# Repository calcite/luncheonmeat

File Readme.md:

# luncheonmeat

## Hardware

Device PCB was designed using KiCAD 5.1. For more info visit KiCAD website [kicad.org](https://kicad.org/download/) 

## Firmware

### Dependencies

```shell
sudo apt-get install gcc-avr binutils-avr avr-libc gdb-avr avrdude
```

> Note: ``ATMega328PB`` is new revision from 2017. avr-libc may not have support for this device. To add support please see how its done in .devcontainer/Dockerfile.

### Build

```shell
cd firmware
make
```

### Flashing

Flashing the device using AVR Dragon ISP:

```shell
make program
```

Set fuses **this is done only once**:

```shell
make program-fuses
```

> Note: ``make`` will internally run ``avrdude`` with correct atributes. 

Bare avrdude flashing command:

```shell
avrdude -p atmega328pb -P usb -c dragon_isp    -U flash:w:luncheonmeat.hex -U eeprom:w:luncheonmeat.eep
```

### Serial Bootloader

Generating ``defines.h`` file:
```shell
cd firmware/bootloader
./preprocessor.sh atmega328pb 2048 PORTB PINB0 8000000 19200
make
make program
make program-fuses
```

Reading target fuses:
```shell
avrdude -p atmega328pb -P usb -c dragon_isp -U efuse:r:-:h
```

To enter bootloader hold ''5'' button and reset the device.

## Resources

- [fuses calculator](http://eleccelerator.com/fusecalc/fusecalc.php?chip=atmega328p&LOW=E2&HIGH=D8&EXTENDED=F7&LOCKBIT=FF)

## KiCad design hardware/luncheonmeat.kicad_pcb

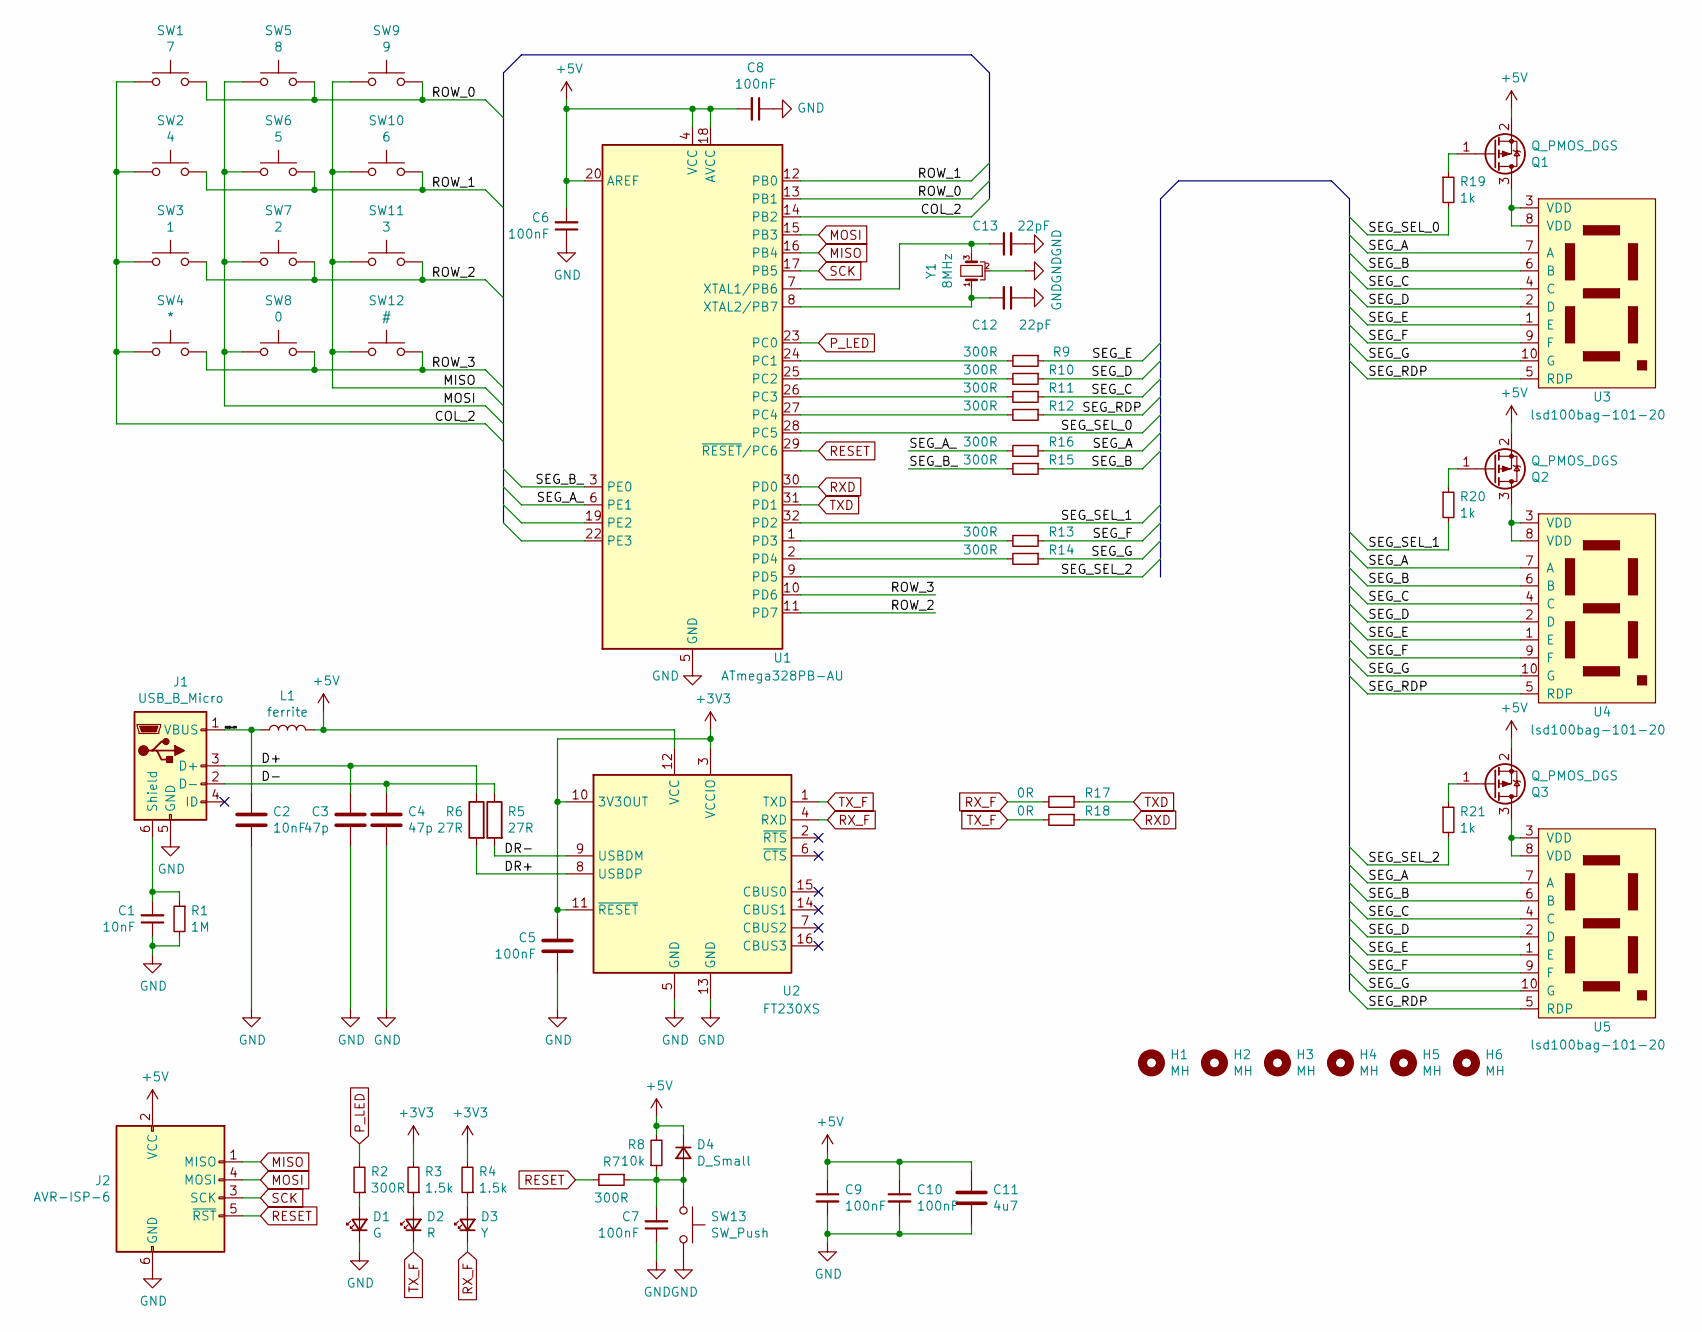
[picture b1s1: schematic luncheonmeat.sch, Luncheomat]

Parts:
C1, C2: 10nF; C_0805_2012Metric_Pad1.18x1.45mm_HandSolder
C3, C4: 47p; C_0805_2012Metric_Pad1.18x1.45mm_HandSolder
C5, C6, C7, C8, C9, C10: 100nF; C_0805_2012Metric_Pad1.18x1.45mm_HandSolder
C11: 4u7; C_0603_1608Metric_Pad1.05x0.95mm_HandSolder
C12, C13: 22pF; C_0603_1608Metric_Pad1.08x0.95mm_HandSolder
D1: G; LED_0805_2012Metric_Castellated
D2: R; LED_0805_2012Metric_Castellated
D3: Y; LED_0805_2012Metric_Castellated
D4: D_Small; D_0805_2012Metric
H1, H2, H3, H4, H5, H6: MH; MountingHole_3.2mm_M3_DIN965
J1: USB_B_Micro; USB_Micro-B_Wuerth_629105150521_CircularHoles
J2: AVR-ISP-6; IDC-Header_2x03_P2.54mm_Vertical
L1: ferrite; L_0805_2012Metric_Pad1.15x1.40mm_HandSolder
Q1, Q2, Q3: Q_PMOS_DGS; SOT-23
R1: 1M; R_0805_2012Metric_Pad1.20x1.40mm_HandSolder
R2, R7, R9, R10, R11, R12, R13, R14, R15, R16: 300R; R_0805_2012Metric_Pad1.20x1.40mm_HandSolder
R3, R4: 1.5k; R_0805_2012Metric_Pad1.20x1.40mm_HandSolder
R5, R6: 27R; R_0805_2012Metric_Pad1.20x1.40mm_HandSolder
R8: 10k; R_0805_2012Metric_Pad1.20x1.40mm_HandSolder
R17, R18: 0R; R_0805_2012Metric_Pad1.20x1.40mm_HandSolder
R19, R20, R21: 1k; R_0805_2012Metric_Pad1.20x1.40mm_HandSolder
SW1: 7; SW_PUSH_6mm
SW2: 4; SW_PUSH_6mm
SW3: 1; SW_PUSH_6mm
SW4: *; SW_PUSH_6mm
SW5: 8; SW_PUSH_6mm
SW6: 5; SW_PUSH_6mm
SW7: 2; SW_PUSH_6mm
SW8: 0; SW_PUSH_6mm
SW9: 9; SW_PUSH_6mm
SW10: 6; SW_PUSH_6mm
SW11: 3; SW_PUSH_6mm
SW12: #; SW_PUSH_6mm
SW13: SW_Push; SW_Push_1P1T_NO_CK_KSC7xxJ
U1: ATmega328PB-AU; TQFP-32_7x7mm_P0.8mm
U2: FT230XS; SSOP-16_3.9x4.9mm_P0.635mm
U3, U4, U5: lsd100bag-101-20; lsd100bag-101
Y1: 8MHz; Crystal_SMD_0603-4Pin_6.0x3.5mm_HandSoldering

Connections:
+3V3: C5.2, R3.2, R4.2, U2.3 (VCCIO), U2.10 (3V3OUT), U2.11 (~RESET)
+5V: C6.2, C8.2, C9.1, C10.1, C11.1, D4.1 (K), J2.2 (VCC), L1.2, Q1.2 (S), Q2.2 (S), Q3.2 (S), R8.2, U1.4 (VCC), U1.18 (AVCC), U1.20 (AREF), U2.12 (VCC)
/COL_2: SW1.2, SW2.2, SW3.2, SW4.2, U1.14 (PB2)
/D+: C3.2, J1.3 (D+), R6.1
/D-: C4.1, J1.2 (D-), R5.1
/DR+: R6.2, U2.8 (USBDP)
/DR-: R5.2, U2.9 (USBDM)
/ROW_0: SW1.1, SW5.1, SW9.1, U1.13 (PB1)
/ROW_1: SW2.1, SW6.1, SW10.1, U1.12 (PB0)
/ROW_2: SW3.1, SW7.1, SW11.1, U1.11 (PD7)
/ROW_3: SW4.1, SW8.1, SW12.1, U1.10 (PD6)
/SEG_A: R16.1, U3.7 (A), U4.7 (A), U5.7 (A)
/SEG_A_: R16.2, U1.6 (PE1)
/SEG_B: R15.1, U3.6 (B), U4.6 (B), U5.6 (B)
/SEG_B_: R15.2, U1.3 (PE0)
/SEG_C: R11.1, U3.4 (C), U4.4 (C), U5.4 (C)
/SEG_D: R10.1, U3.2 (D), U4.2 (D), U5.2 (D)
/SEG_E: R9.1, U3.1 (E), U4.1 (E), U5.1 (E)
/SEG_F: R13.1, U3.9 (F), U4.9 (F), U5.9 (F)
/SEG_G: R14.1, U3.10 (G), U4.10 (G), U5.10 (G)
/SEG_RDP: R12.1, U3.5 (RDP), U4.5 (RDP), U5.5 (RDP)
/SEG_SEL_0: R19.2, U1.28 (PC5)
/SEG_SEL_1: R20.2, U1.32 (PD2)
/SEG_SEL_2: R21.2, U1.9 (PD5)
/USB+5V: C2.2, J1.1 (VBUS), L1.1
GND: C1.1, C2.1, C3.1, C4.2, C5.1, C6.1, C7.1, C8.1, C9.2, C10.2, C11.2, C12.1, C13.2, D1.1 (K), J1.5 (GND), J2.6 (GND), R1.2, SW13.2, U1.5 (GND), U1.21 (GND), U2.5 (GND), U2.13 (GND), Y1.2
MISO: J2.1 (MISO), SW9.2, SW10.2, SW11.2, SW12.2, U1.16 (PB4)
MOSI: J2.4 (MOSI), SW5.2, SW6.2, SW7.2, SW8.2, U1.15 (PB3)
unnamed: C1.2, J1.6 (Shield), R1.1
unnamed: C7.2, D4.2 (A), R7.1, R8.1, SW13.1
unnamed: C12.2, U1.8 (XTAL2/PB7), Y1.1
unnamed: C13.1, U1.7 (XTAL1/PB6), Y1.3
unnamed: D1.2 (A), R2.1
unnamed: D2.2 (A), R3.1
unnamed: D3.2 (A), R4.1
unnamed: Q1.1 (G), R19.1
unnamed: Q1.3 (D), U3.3 (VDD), U3.8 (VDD)
unnamed: Q2.1 (G), R20.1
unnamed: Q2.3 (D), U4.3 (VDD), U4.8 (VDD)
unnamed: Q3.1 (G), R21.1
unnamed: Q3.3 (D), U5.3 (VDD), U5.8 (VDD)
unnamed: R9.2, U1.24 (PC1)
unnamed: R10.2, U1.25 (PC2)
unnamed: R11.2, U1.26 (PC3)
unnamed: R12.2, U1.27 (PC4)
unnamed: R13.2, U1.1 (PD3)
unnamed: R14.2, U1.2 (PD4)
P_LED: R2.2, U1.23 (PC0)
RESET: J2.5 (~RST), R7.2, U1.29 (~RESET~/PC6)
RXD: R18.1, U1.30 (PD0)
RX_F: D3.1 (K), R17.2, U2.4 (RXD)
SCK: J2.3 (SCK), U1.17 (PB5)
TXD: R17.1, U1.31 (PD1)
TX_F: D2.1 (K), R18.2, U2.1 (TXD)

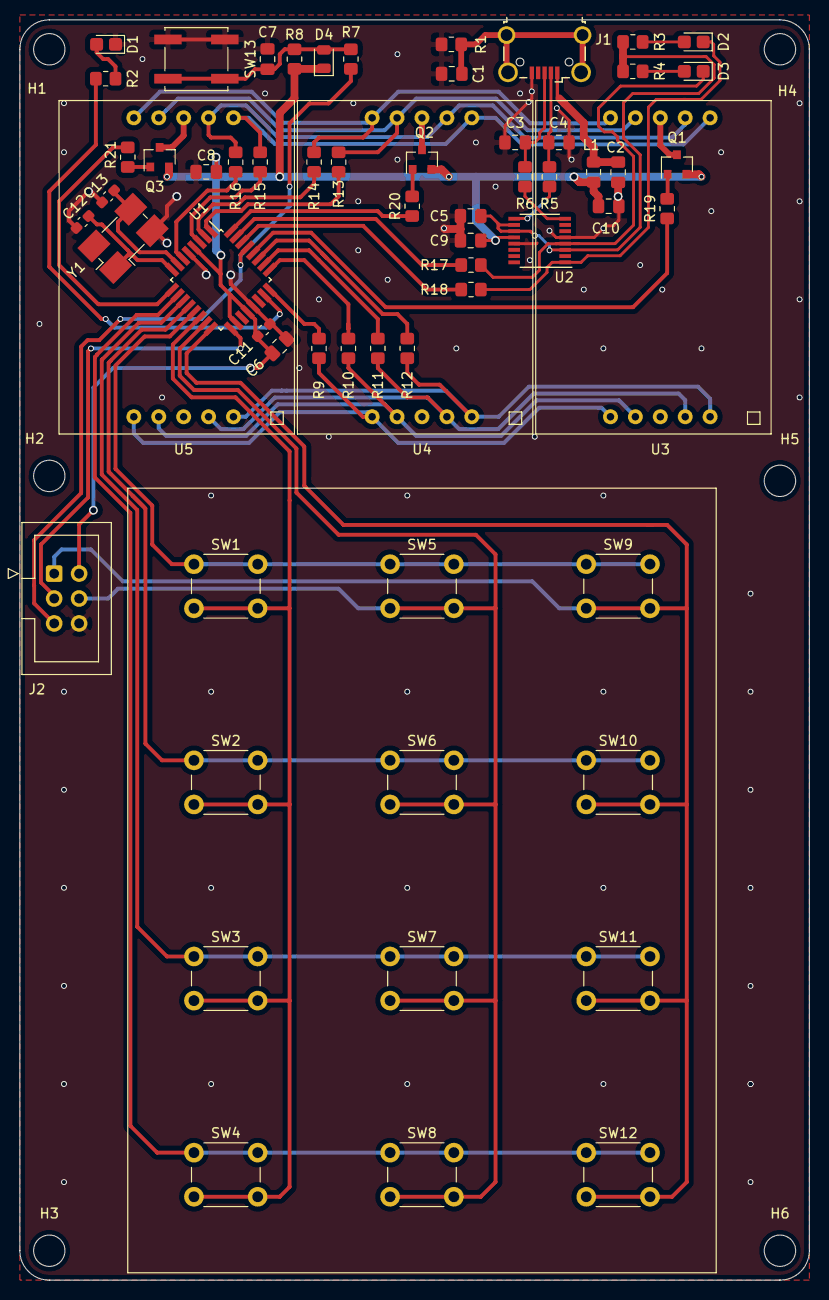
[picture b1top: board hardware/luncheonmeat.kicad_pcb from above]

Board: 2 copper layers, 80.5 x 128.5 mm, 69 parts (0 on the bottom side), 54 nets.

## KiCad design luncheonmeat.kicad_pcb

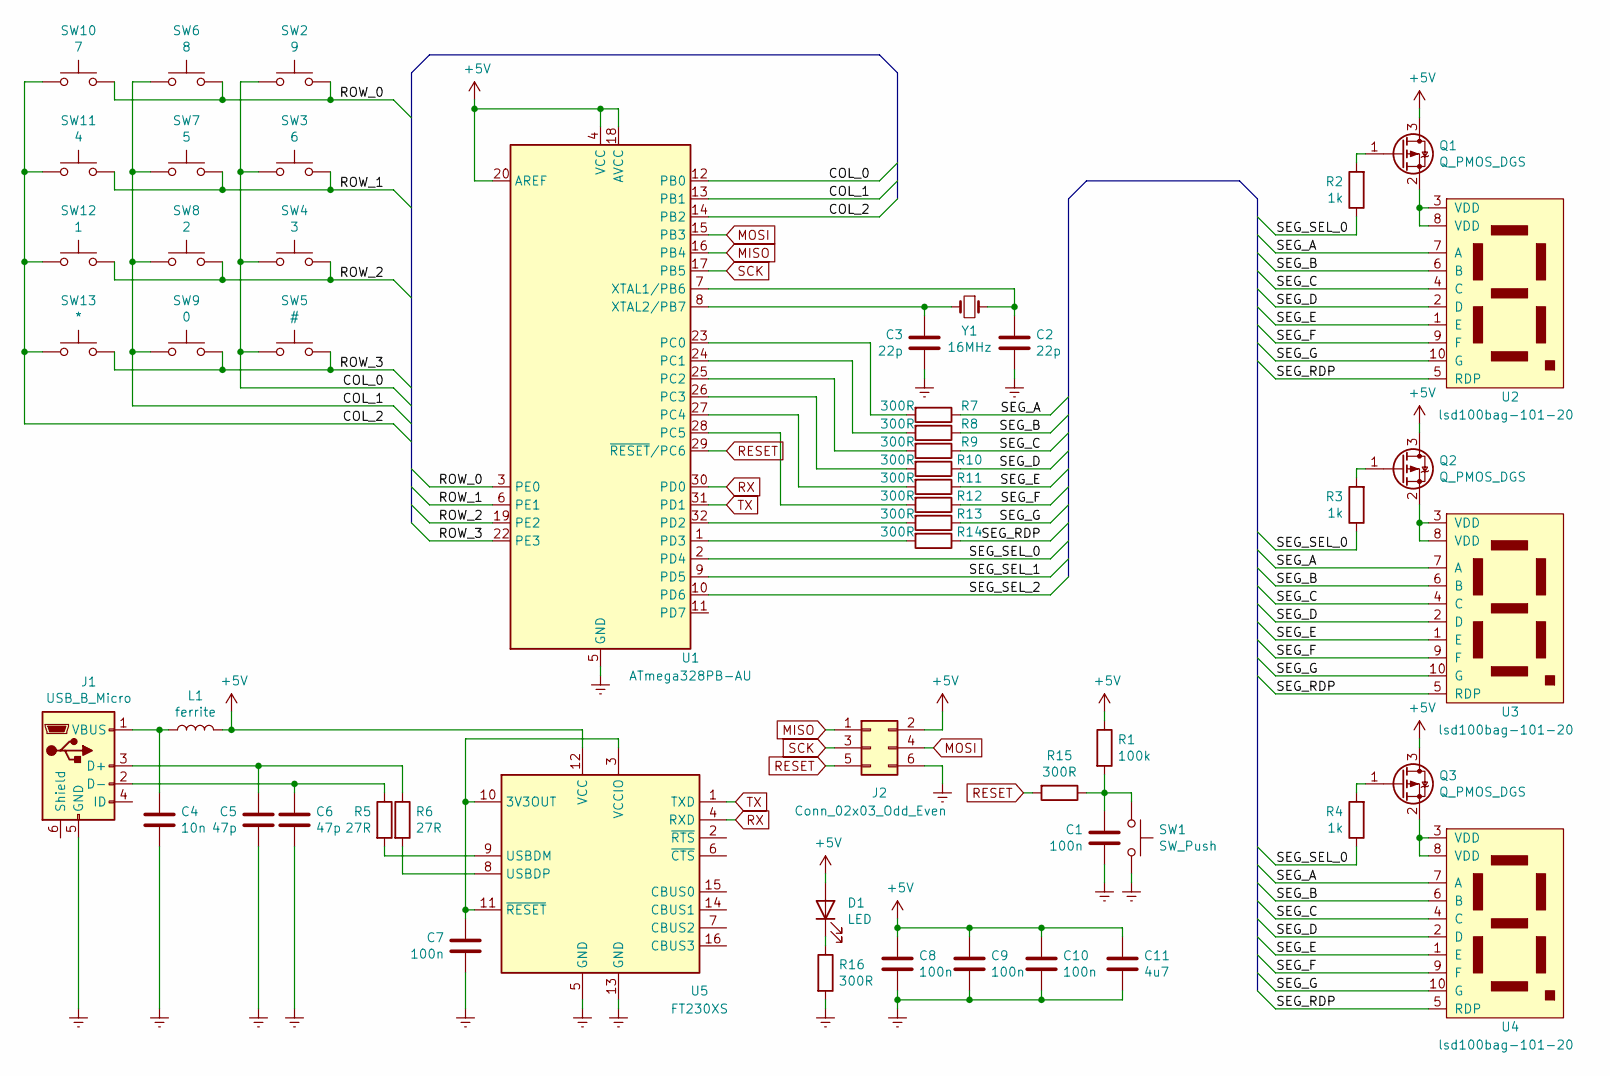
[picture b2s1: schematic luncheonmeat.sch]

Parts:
C1, C7, C8, C9, C10: 100n; C_0603_1608Metric_Pad1.05x0.95mm_HandSolder
C2, C3: 22p; C_0603_1608Metric_Pad1.05x0.95mm_HandSolder
C4: 10n; C_0603_1608Metric_Pad1.05x0.95mm_HandSolder
C5, C6: 47p; C_0603_1608Metric_Pad1.05x0.95mm_HandSolder
C11: 4u7; C_0603_1608Metric_Pad1.05x0.95mm_HandSolder
D1: LED; D_0603_1608Metric_Pad1.05x0.95mm_HandSolder
J1: USB_B_Micro; USB_Micro-B_Wuerth_629105150521_CircularHoles
J2: Conn_02x03_Odd_Even; PinHeader_2x03_P2.54mm_Vertical
L1: ferrite; L_0805_2012Metric_Pad1.15x1.40mm_HandSolder
Q1, Q2, Q3: Q_PMOS_DGS; SOT-23
R1: 100k; R_0603_1608Metric_Pad1.05x0.95mm_HandSolder
R2, R3, R4: 1k; R_0603_1608Metric_Pad1.05x0.95mm_HandSolder
R5, R6: 27R; R_0603_1608Metric_Pad1.05x0.95mm_HandSolder
R7, R8, R9, R10, R11, R12, R13, R14, R15, R16: 300R; R_0603_1608Metric_Pad1.05x0.95mm_HandSolder
SW1: SW_Push; PinHeader_1x02_P2.54mm_Vertical
SW2: 9; SW_PUSH_6mm
SW3: 6; SW_PUSH_6mm
SW4: 3; SW_PUSH_6mm
SW5: #; SW_PUSH_6mm
SW6: 8; SW_PUSH_6mm
SW7: 5; SW_PUSH_6mm
SW8: 2; SW_PUSH_6mm
SW9: 0; SW_PUSH_6mm
SW10: 7; SW_PUSH_6mm
SW11: 4; SW_PUSH_6mm
SW12: 1; SW_PUSH_6mm
SW13: *; SW_PUSH_6mm
U1: ATmega328PB-AU; TQFP-32_7x7mm_P0.8mm
U2, U3, U4: lsd100bag-101-20
U5: FT230XS; SSOP-16_3.9x4.9mm_P0.635mm
Y1: 16MHz; Crystal_HC49-4H_Vertical

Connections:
+5V: C8.1, C9.1, C10.1, C11.1, D1.2 (A), J2.2, L1.2, Q1.3 (D), Q2.3 (D), Q3.3 (D), R1.1, U1.4 (VCC), U1.18 (AVCC), U1.20 (AREF), U5.12 (VCC)
/COL_0: SW2.2, SW3.2, SW4.2, SW5.2, U1.12 (PB0)
/COL_1: SW6.2, SW7.2, SW8.2, SW9.2, U1.13 (PB1)
/COL_2: SW10.2, SW11.2, SW12.2, SW13.2, U1.14 (PB2)
/D+: C5.2, J1.3 (D+), R6.1
/D-: C6.1, J1.2 (D-), R5.1
/DR+: R6.2, U5.8 (USBDP)
/DR-: R5.2, U5.9 (USBDM)
/ROW_0: SW2.1, SW6.1, SW10.1, U1.3 (PE0)
/ROW_1: SW3.1, SW7.1, SW11.1, U1.6 (PE1)
/ROW_2: SW4.1, SW8.1, SW12.1, U1.19 (PE2)
/ROW_3: SW5.1, SW9.1, SW13.1, U1.22 (PE3)
/SEG_A: R7.1, U2.7 (A), U3.7 (A), U4.7 (A)
/SEG_B: R8.1, U2.6 (B), U3.6 (B), U4.6 (B)
/SEG_C: R9.1, U2.4 (C), U3.4 (C), U4.4 (C)
/SEG_D: R10.1, U2.2 (D), U3.2 (D), U4.2 (D)
/SEG_E: R11.1, U2.1 (E), U3.1 (E), U4.1 (E)
/SEG_F: R12.1, U2.9 (F), U3.9 (F), U4.9 (F)
/SEG_G: R13.1, U2.10 (G), U3.10 (G), U4.10 (G)
/SEG_RDP: R14.1, U2.5 (RDP), U3.5 (RDP), U4.5 (RDP)
Earth: C1.1, C2.1, C3.2, C4.1, C5.1, C6.2, C7.1, C8.2, C9.2, C10.2, C11.2, J1.5 (GND), J2.6, R16.2, SW1.2, U1.5 (GND), U1.21 (GND), U5.5 (GND), U5.13 (GND)
MISO: J2.1, U1.16 (PB4)
MOSI: J2.4, U1.15 (PB3)
unnamed: C1.2, R1.2, R15.1, SW1.1
unnamed: C2.2, U1.7 (XTAL1/PB6), Y1.1
unnamed: C3.1, U1.8 (XTAL2/PB7), Y1.2
unnamed: C4.2, J1.1 (VBUS), L1.1
unnamed: C7.2, U5.3 (VCCIO), U5.10 (3V3OUT), U5.11 (~RESET)
unnamed: D1.1 (K), R16.1
unnamed: Q1.1 (G), R2.2
unnamed: Q1.2 (S), U2.3 (VDD), U2.8 (VDD)
unnamed: Q2.1 (G), R3.2
unnamed: Q2.2 (S), U3.3 (VDD), U3.8 (VDD)
unnamed: Q3.1 (G), R4.2
unnamed: Q3.2 (S), U4.3 (VDD), U4.8 (VDD)
unnamed: R7.2, U1.23 (PC0)
unnamed: R8.2, U1.24 (PC1)
unnamed: R9.2, U1.25 (PC2)
unnamed: R10.2, U1.26 (PC3)
unnamed: R11.2, U1.27 (PC4)
unnamed: R12.2, U1.28 (PC5)
unnamed: R13.2, U1.32 (PD2)
unnamed: R14.2, U1.1 (PD3)
RESET: J2.5, R15.2, U1.29 (~RESET~/PC6)
RX: U1.30 (PD0), U5.4 (RXD)
SCK: J2.3, U1.17 (PB5)
TX: U1.31 (PD1), U5.1 (TXD)

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
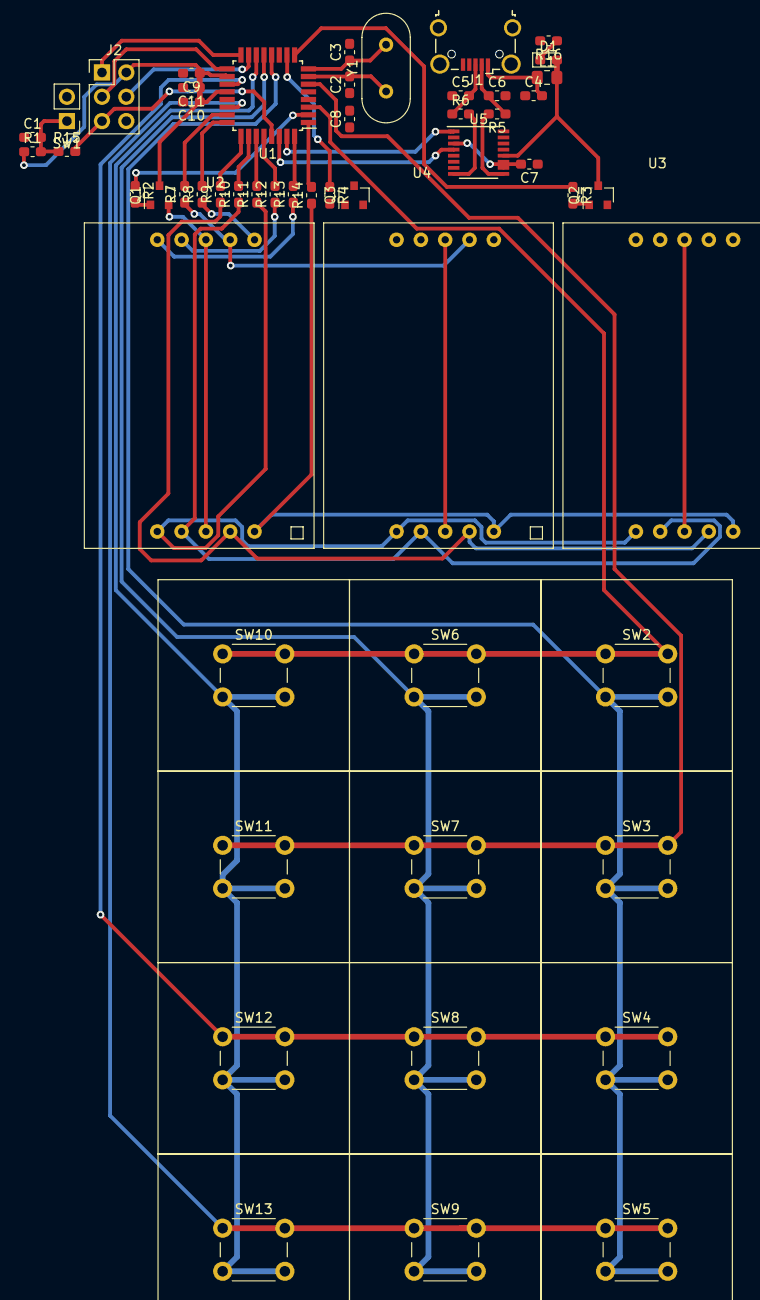
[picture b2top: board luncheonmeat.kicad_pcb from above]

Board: 2 copper layers, 53 parts (0 on the bottom side), 50 nets.

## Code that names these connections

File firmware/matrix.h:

/*
 *  Copyright (C) 2017 Juraj Giertl
 *  All Rights Reserved.
 */
#ifndef _MATRIX_H_
#define _MATRIX_H_

#include <avr/io.h>
#include <stdbool.h>
#include "hw_def.h"

#define ROW_0_PIN		PINB1
#define ROW_1_PIN		PINB0
#define ROW_2_PIN		PIND7
#define ROW_3_PIN		PIND6
#define COL_0_PIN		PINB4
#define COL_1_PIN		PINB3
#define COL_2_PIN		PINB2

#define ROW_0_DDR		DDRB
#define ROW_1_DDR		DDRB
#define ROW_2_DDR		DDRD
#define ROW_3_DDR		DDRD
#define COL_0_DDR		DDRB
#define COL_1_DDR		DDRB
#define COL_2_DDR		DDRB

#define ROW_0_PORT      PORTB
#define ROW_1_PORT      PORTB
#define ROW_2_PORT      PORTD
#define ROW_3_PORT      PORTD
#define COL_0_PORT      PORTB
#define COL_1_PORT      PORTB
#define COL_2_PORT      PORTB

#define IDLE_CNT_MAX 610; // is 20 seconds, s * 30.5 
#define MK_KEY_CLEAR (0x2A)
#define MK_KEY_ENTER (0x23)


#define MK_UNIT_DELAY_MS                    (1)
#define MK_LONG_PUSH_TRESHHOLD_MS           (2000)
#define MK_LONG_PUSH_TRESHHOLD_MS_MAX       (5000)

#define MK_LONG_PUSH_TRESHHOLD ((uint32_t)(MK_LONG_PUSH_TRESHHOLD_MS) / (MK_UNIT_DELAY_MS))
#define MK_LONG_PUSH_TRESHHOLD_MAX ((uint32_t)(MK_LONG_PUSH_TRESHHOLD_MS_MAX) / (MK_UNIT_DELAY_MS))


typedef void (*device_idle)(void);

void matrix_keypad_register_idle_cb(device_idle cb);
void matrix_keypad_idle_reset(void);

bool matrix_keypad_is_enter_key(int8_t key);
bool matrix_keypad_is_clear_key(int8_t key);
bool matric_keypad_is_long_push(uint32_t et_count);

uint32_t matric_keypad_wait_key_release(void);
int8_t matrix_keypad_process(uint32_t *et_count);
void matrix_keypad_init(void);

#endif

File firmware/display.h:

/*
 *  Copyright (C) 2017 Juraj Giertl
 *  All Rights Reserved.
 */
#ifndef _DISPLAY_H_
#define _DISPLAY_H_

#include "hw_def.h"

#define SEG_DISPALY_N_SEGS (3)

#ifdef SEG_DISPLAY_INVERTED
#define seg_a		2//7
#define seg_b		1//6
#define seg_c		4//5
#define seg_d		5//4
#define seg_e		0//3
#define seg_f		7//2
#define seg_g		6//1
#define seg_dp		3//0

/* Segment multiplexing */
#define SEG_POS_0              2
#define SEG_POS_1              1
#define SEG_POS_2              0

#else

#define seg_a		7
#define seg_b		6
#define seg_c		5
#define seg_d		4
#define seg_e		3
#define seg_f		2
#define seg_g		1
#define seg_dp		0

/* Segment multiplexing */
#define SEG_POS_0              0
#define SEG_POS_1              1
#define SEG_POS_2              2
#endif

#define A		0
#define N		1


#define SEG_A_PIN		PINE1
#define SEG_B_PIN		PINE0
#define SEG_C_PIN		PINC3
#define SEG_D_PIN		PINC2
#define SEG_E_PIN		PINC1
#define SEG_F_PIN		PIND3
#define SEG_G_PIN		PIND4
#define SEG_DP_PIN		PINC4

#define SEG_A_DDR		DDRE
#define SEG_B_DDR		DDRE
#define SEG_C_DDR		DDRC
#define SEG_D_DDR		DDRC
#define SEG_E_DDR		DDRC
#define SEG_F_DDR		DDRD
#define SEG_G_DDR		DDRD
#define SEG_DP_DDR		DDRC

#define SEG_A_PORT      PORTE
#define SEG_B_PORT      PORTE
#define SEG_C_PORT      PORTC
#define SEG_D_PORT      PORTC
#define SEG_E_PORT      PORTC
#define SEG_F_PORT      PORTD
#define SEG_G_PORT      PORTD
#define SEG_DP_PORT     PORTC


#define SEG_POS_0_DDR          DDRC
#define SEG_POS_0_PORT         PORTC
#define SEG_POS_0_PIN          PINC5

#define SEG_POS_1_DDR          DDRD
#define SEG_POS_1_PORT         PORTD
#define SEG_POS_1_PIN          PIND2

#define SEG_POS_2_DDR          DDRD
#define SEG_POS_2_PORT         PORTD  
#define SEG_POS_2_PIN          PIND5

#define SEG_DISP_CHAR_CLEAR    (0xFF) // 0xFF

static uint8_t __attribute__((used)) seg_display_chars[18] =
{
	(A << seg_a) | (A << seg_b) | (A << seg_c) | (A << seg_d) | (A << seg_e) | (A << seg_f) | (N << seg_g) | (N << seg_dp),//0
	(N << seg_a) | (A << seg_b) | (A << seg_c) | (N << seg_d) | (N << seg_e) | (N << seg_f) | (N << seg_g) | (N << seg_dp),//1
	(A << seg_a) | (A << seg_b) | (N << seg_c) | (A << seg_d) | (A << seg_e) | (N << seg_f) | (A << seg_g) | (N << seg_dp),//2
	(A << seg_a) | (A << seg_b) | (A << seg_c) | (A << seg_d) | (N << seg_e) | (N << seg_f) | (A << seg_g) | (N << seg_dp),//3
	(N << seg_a) | (A << seg_b) | (A << seg_c) | (N << seg_d) | (N << seg_e) | (A << seg_f) | (A << seg_g) | (N << seg_dp),//4
	(A << seg_a) | (N << seg_b) | (A << seg_c) | (A << seg_d) | (N << seg_e) | (A << seg_f) | (A << seg_g) | (N << seg_dp),//5
	(A << seg_a) | (N << seg_b) | (A << seg_c) | (A << seg_d) | (A << seg_e) | (A << seg_f) | (A << seg_g) | (N << seg_dp),//6
	(A << seg_a) | (A << seg_b) | (A << seg_c) | (N << seg_d) | (N << seg_e) | (N << seg_f) | (N << seg_g) | (N << seg_dp),//7
	(A << seg_a) | (A << seg_b) | (A << seg_c) | (A << seg_d) | (A << seg_e) | (A << seg_f) | (A << seg_g) | (N << seg_dp),//8
	(A << seg_a) | (A << seg_b) | (A << seg_c) | (A << seg_d) | (N << seg_e) | (A << seg_f) | (A << seg_g) | (N << seg_dp),//9
	(A << seg_a) | (A << seg_b) | (A << seg_c) | (N << seg_d) | (A << seg_e) | (A << seg_f) | (A << seg_g) | (N << seg_dp),//A ,10
	(A << seg_a) | (A << seg_b) | (A << seg_c) | (A << seg_d) | (A << seg_e) | (A << seg_f) | (A << seg_g) | (N << seg_dp),//B ,11
	(A << seg_a) | (N << seg_b) | (N << seg_c) | (A << seg_d) | (A << seg_e) | (A << seg_f) | (N << seg_g) | (N << seg_dp),//C ,12
	(A << seg_a) | (A << seg_b) | (A << seg_c) | (A << seg_d) | (A << seg_e) | (A << seg_f) | (N << seg_g) | (N << seg_dp),//D ,13
	(A << seg_a) | (N << seg_b) | (N << seg_c) | (A << seg_d) | (A << seg_e) | (A << seg_f) | (A << seg_g) | (N << seg_dp),//E ,14
	(A << seg_a) | (N << seg_b) | (N << seg_c) | (N << seg_d) | (A << seg_e) | (A << seg_f) | (A << seg_g) | (N << seg_dp),//F ,15
	(A << seg_a) | (A << seg_b) | (N << seg_c) | (N << seg_d) | (N << seg_e) | (A << seg_f) | (A << seg_g) | (N << seg_dp),//degree
	(N << seg_a) | (N << seg_b) | (N << seg_c) | (N << seg_d) | (N << seg_e) | (N << seg_f) | (A << seg_g) | (N << seg_dp),//minus

};

void seg_display_wait_animation(uint8_t from, uint8_t to, uint16_t speed);

void seg_dispaly_set_digits(uint8_t d2, uint8_t d1, uint8_t d0);
void seg_dispaly_set_dec_num(uint16_t num);

void seg_display_draw_circle(void);
void seg_display_draw_line(void);
void seg_display_clear(void);

void seg_display_set_contrast(uint8_t val);

void seg_display_init(void);

#endif

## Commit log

2020-10-08 pushing it all
2020-10-09 progress
2020-12-15 late
2020-12-21 v0.1.0 Initial release to ALCZ git. Created file structures.
2020-12-21 Fix schematic, new board layout
2020-12-22 v0.2.0, PCB board finished
2021-01-08 v0.2.1 PCB Updated
2021-01-15 v0.2.2 PCB Updated
2021-01-19 v0.2.3 PCB Updated, board step file generated
2021-01-19 v0.2.4 PCB Updated
2021-01-19 update step file
2021-01-22 add firmware base
2021-01-25 [ADD] avr109 bootloader source
2021-01-25 [ADD] support for atmega328pb device
2021-02-16 USART working
2021-02-17 add display code
2021-02-17 add key matrix code
2021-02-17 implementing main rutine
2021-02-18 Added animations for display interface, cleanup matrix code
2021-02-18 add simple transport protocol, integrate with main program
2021-02-18 Release v0.3.0 update readme and changelog, enable epprom flashing,
2021-02-22 Release v0.4.0 - see changelog for more info.
2021-02-22 Release v0.4.1 fix multiplex
2021-03-03 Release v0.4.2
2021-03-03 Add LICENSE
2021-03-04 Release v0.4.3 - add clear command - alow sending zero
2021-03-04 Release v0.4.4 - added AVR109 bootloader for atmega328pb
